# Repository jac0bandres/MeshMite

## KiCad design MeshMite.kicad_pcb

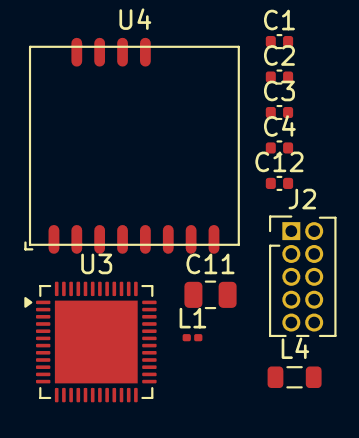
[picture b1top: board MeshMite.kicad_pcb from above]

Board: 4 copper layers, 11 parts (0 on the bottom side), 17 nets, no tracks yet.

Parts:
C1, C4, C12: 100 nF; C_0402_1005Metric
C2: 47 nF; C_0402_1005Metric
C3: 1.0 uF; C_0402_1005Metric
C11: 100 pF; C_0805_2012Metric
J2: Conn_ARM_JTAG_SWD_10; PinHeader_2x05_P1.27mm_Vertical
L1: 15 nH; L_0201_0603Metric
L4: 10 uH; L_0805_2012Metric
U3: nRF52840; QFN-48-1EP_6x6mm_P0.4mm_EP4.6x4.6mm
U4: Wio-SX1262; Wio-SX11262_footprint

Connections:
+3V3: C4.1, C12.2, U3.12 (VDD), U3.37 (VDD), U4.8 (VCC)
/LORA_BUSY: U3.10 (P0.11), U4.11 (BUSY)
/LORA_DIO: U3.11 (P0.12), U4.12 (DIO1)
/LORA_MISO: U3.8 (P1.08), U4.2 (MISO)
/LORA_MOSI: U3.7 (P0.08), U4.3 (MOSI)
/LORA_NRST: U3.5 (P0.05), U4.5 (RST)
/LORA_NSS: U3.4 (P0.04), U4.6 (NSS)
/LORA_RF_SW: U3.9 (P1.09), U4.1 (RF_SW1)
/LORA_SCK: U3.6 (P0.07), U4.4 (SCK)
/RESET: J2.10 (~RESET), U3.16 (P0.18)
/SWCLK: J2.4 (SWCLK/TCK), U3.27 (SWDCLK)
/SWDIO: J2.2 (SWDIO/TMS), U3.26 (SWDIO)
/VTref: J2.1 (VTref), U3.25 (VDD)
GND: C1.1, C2.1, C2.2, C3.1, C3.2, C4.2, C11.1, C11.2, C12.1, J2.3 (GND), J2.5 (GND), J2.9 (GNDDetect), L1.2, U3.33 (DEC6), U3.45 (VSS), U3.46 (DEC4), U3.49 (VSS), U4.7 (GND1)
unnamed: L1.1, L4.2
unnamed: L4.1, U3.47 (DCC)
unnamed: C1.2, U3.1 (DEC1)

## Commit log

2026-03-10 first
2026-03-13 modularize
